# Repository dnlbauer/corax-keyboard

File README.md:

# Corax: A column-staggered fully-wireless split keyboard with scrollwheels.

- Choc-spaced, hot-swappable
- Two versions: with 56 or 54 keys
- Scrollwheel (EVQWGD001) on both sides
- Strong pinky stagger (0.66) and a 5 deg. pinky splay
- Fully wireless built for Nice!Nano + ZMK (no TRRS Jack)
- Nice!View support (5 pin connector)
- Reversible PCB
- 3d printable magnetic case, switchplate and MCU cover 

## Gallery

## Corax56 vs Corax54

I initially designed the Corax56 (=56 keys) with 4 pinky keys. The upper key (usually mapped to ESC) was placed in a new column because I found it easier to reach horizontally than vertically.
Over the time, I realized that I am not using this button very often. The Corax54 was born as a more compact version where the pinky cluster misses this additonal column and has only 54 keys (2 less). This is the only difference between the two versions.

## Firmware

Natively supports [ZMK](https://zmk.dev/). The firmware for the Corax56 and Corax56 can be found in the submodule and is available here: https://github.com/dnlbauer/corax-zmk-config

## Build guide

[see here](./docs/BuildGuide.md)

## Standing on the shoulders of giants

- A great tutorial I referenced a lot by FlatFootFox: https://flatfootfox.com/ergogen-introduction/
- Lots of inspiration and ideas for this project came from these boards: [Choccy](https://github.com/sprengboard/choccy), [Sofle](https://github.com/josefadamcik/SofleKeyboard), [brain](https://github.com/Wesztman/brain), [spleeb](https://github.com/chrishoage/spleeb)

## License

This project is licensed under the MIT License - see the [LICENSE](LICENSE) file for details.

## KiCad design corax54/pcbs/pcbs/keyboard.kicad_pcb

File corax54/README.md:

# Corax54

## Bill of materials

**Essentials**:
| **Item**                        | **Count** | **Note** |
|---------------------------------|-----------|----------|
| Keyboard PCB                    | 2         |          |
| Nice!Nano                       | 2         |          |
| 12 pin headers and sockets      | 4         | You can use through-hole diode legs as pins. Sockets spacing: 2.54mm, Socket height: Using minimal height sockets might not leave enough room to mount the battery under the MCU. 3DS1002-01-1*20V13-JK by CONNFLY are a good choice, but you can also use lower ones and longer legs instead. Spiltkb has a good [guide on mounting](https://docs.splitkb.com/hc/en-us/articles/360011263059).  |
| LiPo battery (301230)           | 2         | 110mAh   |
| Kailh Choc v1 switches (PG1350) | 54        |          |
| Keycaps                         | 54        |          |
| Kailh Choc hotswap sockets      | 54        |          |
| Encoder EVQWGD001               | 2         |          |
| Diodes 1N4148W                  | 56        | for each key + encoder |
| Buttons                         | 2         | reset buttons; 2 pins through-hole, tactile, 3x6x4.3mm |
| Slider Switches                 | 2         | on/off switches; SMD, C128955 |
| USB-C Cable                     | 1         | for copying the firmware 

**Optional (Displays, 3d printed case)**:

| **Item**                        | **Count** | **Note** |
|---------------------------------|-----------|----------|
| Nice!View + mounts              | 2         |          |
| Switchplate                     | 2         | Height: 1.2mm; either 3d printed or cut pcbs. [stl](./3dprints/switchplate/) |
| Case (Left + Right)             | 1         | see [here](./3dprints/case/).   |
| Silicone feet                   | 8         |          |

## Firmware

The firmware repository can be found here: [https://github.com/dnlbauer/corax54-zmk-config](https://github.com/dnlbauer/corax54-zmk-config).

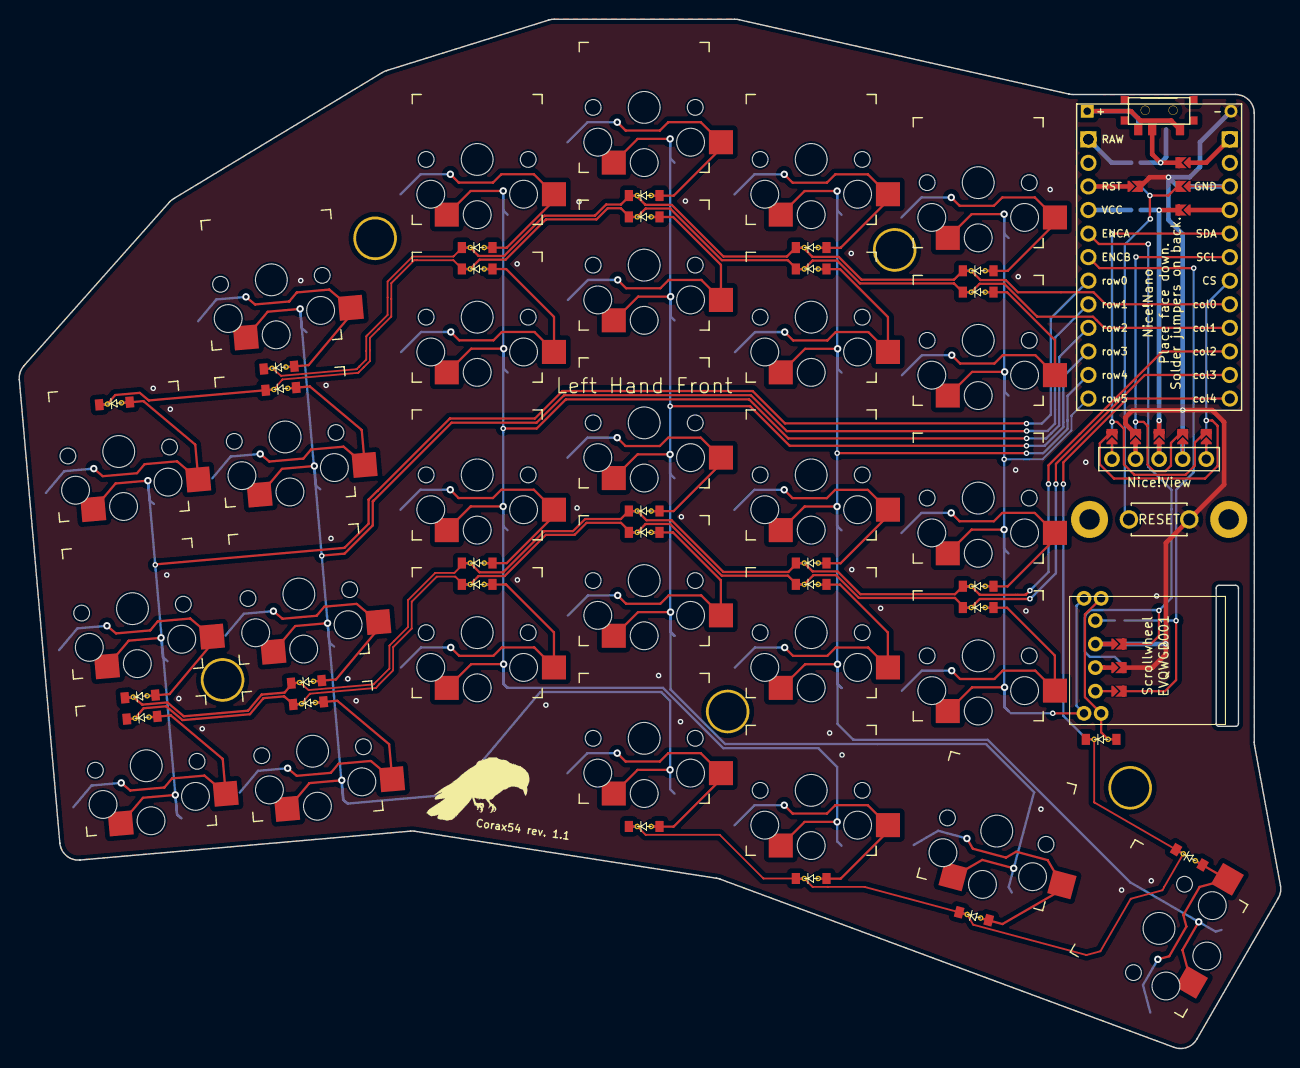
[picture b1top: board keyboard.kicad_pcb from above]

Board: 2 copper layers, 136.0 x 110.9 mm, 90 parts (0 on the bottom side), 60 nets.

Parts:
D1, D2, D3, D4, D5, D6, D7, D8, D9, D10, D11, D12, D13, D14, D15, D16, D17, D18, D19, D20, D21, D22, D23, D24, D25, D26, D27, D28: ComboDiode
J1, J2, J3, J4, J5, J6, J7, J8, J9, J10, J11, J12, J13, J14, J15, J16, J17, J18, J19, J20, J21, J22, J23, J24: Jumper
MCU1: ProMicro
Nice!View1: niceview_headers
S1, S2, S3, S4, S5, S6, S7, S8, S9, S10, S11, S12, S13, S14, S15, S16, S17, S18, S19, S20, S21, S22, S23, S24, S25, S26, S27: PG1350
T1: SPDT_C128955
_1: ResetSW
_2, _3, _4, _5, _6, _7, _8: Hole

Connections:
CS: J19.2, J24.2, MCU1.19
ENCA: J3.2, J6.2, MCU1.5
ENCA_GND: J3.1, J5.1
ENCB: J1.2, J4.2, MCU1.6
GND: J2.2, J5.2, J10.2, J14.2, J18.2, J23.2, _1.2
GND_ENCA: J2.1, J6.1
GND_RST: J10.1, J12.1, MCU1.15
GND_VCC: J13.1, MCU1.16
NN_CS_SDA: J19.1, J20.1, Nice!View1.1
NN_GND_SCL: J18.1, J21.1, Nice!View1.1
NN_SCL_GND: J16.1, J23.1, Nice!View1.3
NN_SDA_CS: J15.1, J24.1, Nice!View1.4
NN_VCC: J17.1, J22.1, Nice!View1.2
P1_RAW: J11.1, MCU1.13
RAW: J7.2, J11.2, T1.2
RAW_P1: J7.1, MCU1.1
RST: J8.2, J12.2, _1.1
RST_GND: J8.1, J14.1, MCU1.3
SCL: J16.2, J21.2, MCU1.18
SDA: J15.2, J20.2, MCU1.17
VCC: J9.2, J13.2, J17.2, J22.2
VCC_GND: J9.1, MCU1.4
col0: D3.1, D5.1, D8.1, D11.1, D13.1, MCU1.20
col1: D16.1, D18.1, D20.1, D22.1, D24.1, D26.1, MCU1.21
col2: D1.1, D2.1, D4.1, D7.1, D10.1, D12.1, MCU1.22
col3: D15.1, D17.1, D19.1, D21.1, D23.1, D25.1, MCU1.23
col4: D6.1, D9.1, D14.1, D27.1, D28.1, MCU1.24
index_bottom: D23.2, S18.2
index_home: D10.2, S19.2
index_mod: D9.2, S17.2
index_num: D11.2, S21.2
index_top: D24.2, S20.2
inner_bottom: D25.2, S22.2
inner_home: D12.2, S23.2
inner_num: D13.2, S25.2
inner_top: D26.2, S24.2
layer_cluster: D14.2, S26.2
middle_bottom: D21.2, S13.2
middle_home: D7.2, S14.2
middle_mod: D6.2, S12.2
middle_num: D8.2, S16.2
middle_top: D22.2, S15.2
outer_bottom: D15.2, S1.2
outer_home: D1.2, S2.2
outer_top: D16.2, S3.2
pinky_bottom: D17.2, S4.2
pinky_home: D2.2, S5.2
pinky_num: D3.2, S7.2
pinky_top: D18.2, S6.2
ring_bottom: D19.2, S8.2
ring_home: D4.2, S9.2
ring_num: D5.2, S11.2
ring_top: D20.2, S10.2
row0: MCU1.7, S1.1, S2.1, S3.1
row1: MCU1.8, S4.1, S5.1, S6.1, S7.1, S12.1
row2: MCU1.9, S8.1, S9.1, S10.1, S11.1, S17.1
row3: MCU1.10, S13.1, S14.1, S15.1, S16.1, S26.1
row4: MCU1.11, S18.1, S19.1, S20.1, S21.1, S27.1
row5: MCU1.12, S22.1, S23.1, S24.1, S25.1
space_cluster: D27.2, S27.2

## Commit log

2023-06-04 button placement
2023-06-04 outlines
2023-06-04 place some components on pcb
2023-06-04 better nicenano positioning
2023-06-04 work on button placement
2023-06-05 stagger and button placement
2023-06-06 splay 5+5; thumb cluster vertical dist
2023-06-08 remove index mod button
2023-06-08 naming things
2023-06-08 shift thumbcluster, remove controller
2023-06-08 reduce pinky stagger to 0.33
2023-06-08 more thumb cluster arcing
2023-06-10 more work on the thumb cluster arcing
2023-06-10 move thumb cluster down
2023-06-10 make thumb cluster similar to sofle choc; more stagger on index
2023-06-11 shrink thumbcluster and move splayed columns closer together
2023-06-11 syntax
2023-06-11 reverse keys
2023-06-11 move thumbcluster a bit closer
2023-06-11 add promicro
2023-06-12 define row and column net for switches
2023-06-13 scrollwheel/rotary
2023-06-13 rotate scrollwheel, fix outline
2023-06-17 add niceview
2023-06-17 add diodes without through_holes
2023-06-17 gitignore
2023-06-18 use vias for diodes
2023-06-18 icnr. niceview distance for more battery space
2023-07-01 remove pinky stagger
2023-07-01 rotary legs removed + diode placement
2023-07-01 keyboard placement
2023-07-01 nicenano placement closer to keys
2023-07-02 refine board polygon
2023-07-02 increase mcu pcu padding
2023-07-02 reposition encoder
2023-07-02 reposition scrollwheel again
2023-07-02 position diodes close to pad
2023-07-02 move up outer2 button
2023-07-02 switch and battery connection
2023-07-02 reset
2023-07-05 fix scroll wheel net
2023-07-05 swap row and col pins
2023-07-07 move diodes below keys
2023-07-07 add screw holes
2023-07-07 add plexiglas holes and move reset
2023-07-09 rotate switches and adjust components to rotated switches
    commit d4ba6b622321e3bd7a7089699f45bbde7e819468
    Author: daniel <github@dbauer.me>
    Date: Sun Jul 9 12:29:10 2023 +0200
    adjust screw holes
    commit 41602ad8a8b55815b8c0b4ff7b805927a1cf0c3f
    Author: daniel <github@dbauer.me>
2023-07-09 rotate scroll diode
2023-07-09 mirror switches and place diodes
2023-07-09 add mcu jumper
2023-07-09 mirror slider
2023-07-09 mcu jumper
2023-07-09 add mcu+batt labels to back of board
2023-07-09 add nicenano labels
2023-07-09 fix mcu jumper net
2023-07-09 add niceview jumper
2023-07-09 text saying where to solder
2023-07-09 add label for left and right hand
2023-07-10 swap jumpers side to solder-on-back
2023-07-10 adjust jumper labels
2023-07-10 increase nice view jumper distance from mcu
2023-07-10 re-add square around nicenano raw pin, but only on relevant side
2023-07-11 fancy jumper
2023-07-11 mcu labels
2023-07-11 nice view outline
2023-07-11 move diodes to center
2023-07-13 mirror scrollwheel
2023-07-15 move outer pinky
2023-07-15 move scrollwheel down a bit
2023-07-15 adjust screw holes
2023-07-15 add fillet
2023-07-16 mcu distances
2023-07-16 incr. pinky stagger to 0.66
2023-07-16 incr. index stagger to 0.33
2023-07-16 footprint
2023-07-16 group diodes together
2023-07-16 adjust screw holes to new staggering
2023-07-17 add some text and descriptions
2023-07-17 screw hole sizes
2023-07-17 kicad
2023-07-17 preview
2023-07-17 license
2023-07-17 schematic overview
2023-07-17 remove cache file
2023-07-17 add wip warning
2023-07-18 change prototype image
2023-07-18 fixed some drc problems Squashed commit of the following:
    commit fc0171f96f06824f930dc5825498fa5e5ecf1060
    Author: daniel <github@dbauer.me>
    Date: Tue Jul 18 11:26:57 2023 +0200
    reversible slider
    commit 837158be306a0aa2e166f52b0d32387ab34f280f
    Author: daniel <github@dbauer.me>
2023-07-18 define screw holes as points
2023-07-18 remove unused outlines
2023-07-18 switchplate
2023-07-18 build file
2023-07-18 incr. switchplate tolerance around scrollwheel
2023-07-18 create step files from build script
2023-07-18 add step files
2023-07-19 kicad 7.0.6
2023-07-19 gerbers
2023-07-19 add missing connection
2023-07-19 add ground vias
2023-07-19 switchplate distances
2023-07-19 images
2023-07-19 add more ground vias
2023-07-19 add order pcb number
2023-07-20 initial zmk config based on sofle
2023-07-20 diode direction
2023-07-20 work on keymap and keyboard gpios
2023-07-21 add niceview adapter and reduce complexity
2023-07-21 cleanup
2023-07-21 scrollwheel
2023-07-22 transformation matrix
2023-07-22 test keymap
2023-07-24 move config to own repo
2023-07-24 Revert "move config to own repo"
    This reverts commit 26e8e8c18cc8e3df8428cc425f9dfedfb6ce8e9e.
2023-07-24 move zmk config to own repo
2023-07-24 add zmk config as submodule
2023-07-29 zmk config
2023-07-29 switchplate stl
2023-07-29 zmk config track main head
2023-07-30 cleanup pcb folder
2023-07-30 build script
2023-07-30 images and BOM
2023-07-30 add images
2023-07-30 3d printed case
2023-07-30 3d printed case image sizes
2023-07-30 case BOM
2023-08-02 update config ref
2023-08-02 update gitignore
2023-08-02 add mcu cover
2023-08-02 better images
2023-08-03 Update LICENSE
2023-08-05 incr. diode to socket distance
2023-08-05 fix mcu labels
2023-08-05 make text on pcb better readable
2023-08-05 add rev and order number to ergogen config
2023-08-05 routed rev 1.1
2023-08-05 add icon svg
2023-08-05 pcb render
2023-08-05 update gerbers
2023-08-05 Squashed commit of the following:
    commit bb18cddcc8a03dbf4a5a163c8480892c78f4e76d
    Author: daniel <github@dbauer.me>
    Date: Sat Aug 5 11:43:33 2023 +0200
    update gerbers
    commit df5ee882de9ff45955de45abaf159e16f07e81d5
    Author: daniel <github@dbauer.me>
2023-08-12 actions: ergogen
2023-08-12 actions: ergogen (#1)
    * actions: ergogen
    * Update ergogen.yaml
    * Update ergogen.yaml
    * Update ergogen.yaml
    * Update ergogen.yaml
    * Update ergogen.yaml
2023-09-23 update firmware ref
2023-10-24 update config
2024-01-29 update images
2024-01-29 update config link
2024-02-09 build into correct folder
2024-02-10 add ergogen package
2024-02-10 corax54 pcbs
2024-02-10 move corax56 in own folder
2024-03-10 update zmk config
2024-03-26 case stls
2024-03-29 clean pcb folder
2024-03-29 3dprints
2024-03-29 add switchlate step file
2024-03-29 update READMEs
2024-03-29 remove github actions
2024-03-29 build guide
2024-03-30 pcb ordering
2024-05-04 remove old zmk references
2024-05-04 zmk config update
2024-05-04 Update README.md with firmware link
